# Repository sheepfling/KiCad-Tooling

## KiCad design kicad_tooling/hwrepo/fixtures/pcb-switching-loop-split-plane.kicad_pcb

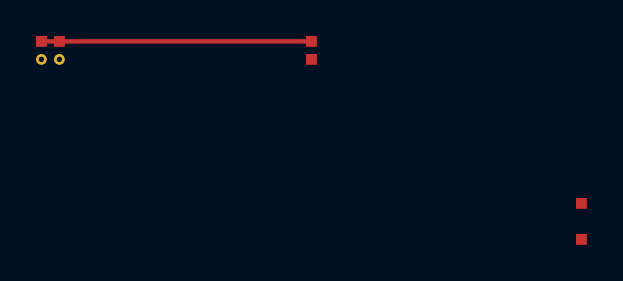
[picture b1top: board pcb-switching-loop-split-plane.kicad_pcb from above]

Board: 4 copper layers, 4 parts (0 on the bottom side), 2 nets.

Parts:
C1, C2: 100nF; Cap_0603
C3: Rotated; Cap_0603
U1: SyntheticIC; IC_QFN

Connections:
GND: C1.2, C2.2, C3.2, U1.2
VDD: C1.1, C2.1, C3.1, U1.1
